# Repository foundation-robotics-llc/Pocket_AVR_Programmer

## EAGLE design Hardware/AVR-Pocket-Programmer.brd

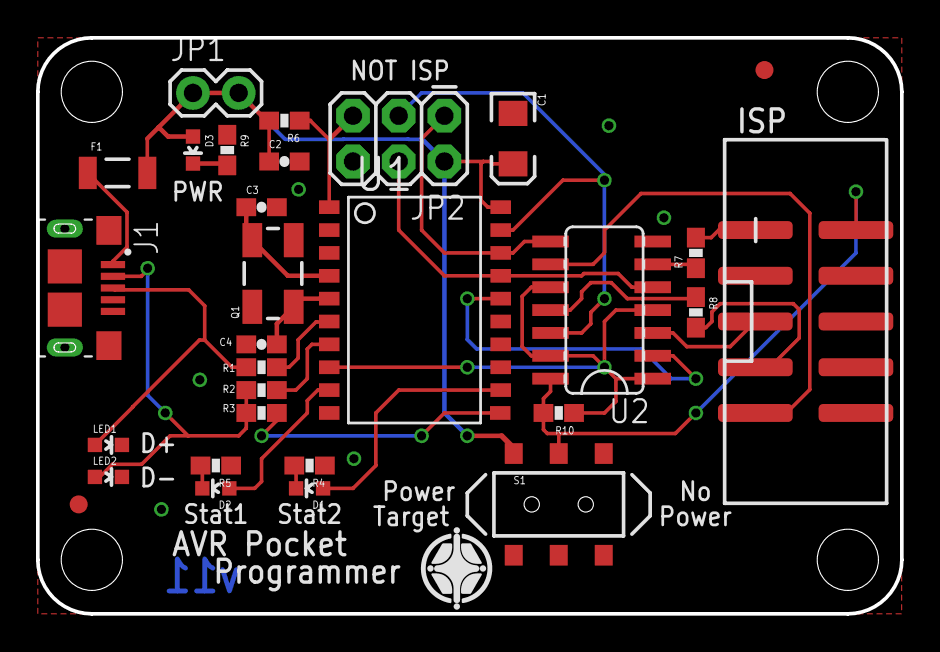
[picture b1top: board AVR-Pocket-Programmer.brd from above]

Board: 2 copper layers, 48.0 x 32.0 mm, 31 parts (0 on the bottom side), 28 nets.

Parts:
C1: 10uF; EIA3216
C2: 0.1uF; 0603-CAP
C3, C4: 22pF; 0603-CAP
D1, D3: Blue; LED-0603
D2: Red; LED-0603
F1: 500mA; PTC-1206-WIDE
FRAME1: FRAME-LETTER; CREATIVE_COMMONS
J1: 10118193-0001LF; FCI_10118193-0001LF
JP1: Power Select; 1X02
JP2: AVR_SPI_PRG_6PTH; 2X3
JP3: AVR_SPI_PROG2SHROUDED_SMD; 2X5-SHROUDED_SMD
LED1, LED2: Blue; LED-0603
Q1: 12 MHz; CRYSTAL-SMD-5X3
R1, R2: 27; 0603-RES
R3: 1.5K; 0603-RES
R4, R5, R6, R9: 1K; 0603-RES
R7, R8: 100; 0603-RES
R10: 22K; 0603-RES
S1: Power Select; AYZ0202
U1: ATTINY2313-20S; SO20L
U2: 74ACT125D; SO014
U$6, U$7: FIDUCIAL1X2; FIDUCIAL-1X2

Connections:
CTL: R10.1, U1.8, U2.1, U2.4, U2.10, U2.13
D+: J1.3, LED1.A, R1.1
D-: J1.2, LED2.A, R2.1, R3.1
GND: C1.C, C2.2, C3.2, C4.2, J1.5, JP2.6, JP3.4, JP3.6, JP3.8, JP3.10, LED1.C, LED2.C, R4.1, R5.1, R9.1, U1.10, U2.7
MISO': JP2.1, U1.18, U2.8
MOSI': JP2.4, U1.17, U2.5
unnamed: R3.2, U1.11
unnamed: D2.A, U1.9
unnamed: D3.C, R9.2
unnamed: F1.1, J1.1
unnamed: C3.1, Q1.3, U1.4
unnamed: C4.1, Q1.1, U1.5
unnamed: D1.A, U1.12
unnamed: D1.C, R4.2
unnamed: D2.C, R5.2
unnamed: R7.1, U2.6
unnamed: R8.1, U2.11
PD+: R1.2, U1.6
PD-: R2.2, U1.7
RST: JP2.5, R6.1, U1.1
RST': U1.16, U2.2
SCK': JP2.3, U1.19, U2.12
TARGET-MISO: JP3.9, U2.9
TARGET-MOSI: JP3.1, R7.2
TARGET-PWR: JP3.2, R10.2, S1.2, U2.14
TARGET-RST: JP3.5, U2.3
TARGET-SCK: JP3.7, R8.2
VCC: C1.A, C2.1, D3.A, F1.2, JP1.1, JP1.2, JP2.2, R6.2, S1.1, U1.20

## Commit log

2019-07-18 Removed branding and updated docs
2019-07-23 Board Updated
    - Resized and rounded edges
    - Changed to USB Micro B
    - Moved some wires to fit Error Check
2019-07-27 Added logos
2019-09-04 Move labels that were in keep outt

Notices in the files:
parts and their libraries:
SparkFun-Aesthetics: Licensing: CC v3.0 Share-Alike You are welcome to use this library for commercial purposes.
SparkFun-Aesthetics: Released under the Creative Commons Attribution Share-Alike 3.0 License
SparkFun-Aesthetics: http://creativecommons.org/licenses/by-sa/3.0
